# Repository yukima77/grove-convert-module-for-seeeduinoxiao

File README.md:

# Grove Convert Module for Seeeduino XIAO v1.0

Seeeduino XIAO用のGrove拡張基板です。

## 注意

本ページは基板に「Grove Convert Module for Seeeduino XIAO」という名称で書かれた基板用です。

シルク等の修正を行った「EdelBoard for Seeeduino XIAO」とかかれた基板は、下記ページを参照して下さい。
https://github.com/yukima77/edelboard-for-seeeduinoxiao

## 特長
入出力用・シリアル用・ws2812b/サーボモータ用の3つのコネクタが付いているシンプルな基板です。

Seeeduino XIAOを直付けすることによって、ピンヘッダーがあるときより薄くして使うこともできます。

ピン配置及び形状互換のAdafruit QT Pyも問題なく接続できます。

## スペック

基板サイズ（コネクタ込）：42.0×24.0×11.6 mm

## ピン

背面上部(ws2812b/サーボモータ用)：GND/VCC/D5(P5)/D4(P4)  
背面右部(シリアル用)：GND/3V3/TX(P6)/RX(P7)  
背面左部(入出力用)：GND/3V3/P1/P0

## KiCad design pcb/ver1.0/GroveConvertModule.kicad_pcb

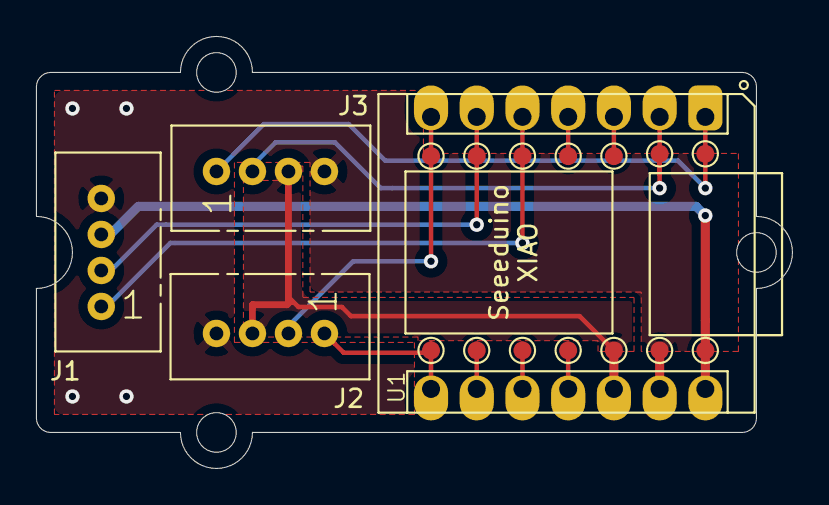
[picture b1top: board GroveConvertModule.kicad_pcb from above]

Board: 2 copper layers, 42.0 x 24.0 mm, 4 parts (0 on the bottom side), 9 nets.

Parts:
J1, J2, J3: Conn_01x04; Grove_1x04
U1: Seeeduino XIAO-MOUDLE14P-2.54-21X17.8MM_Header

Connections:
/3V3: J2.3, J3.3, U1.12
/5V: J1.3, U1.14
/A0_D0: J3.1, U1.1
/A1_D1: J3.2, U1.2
/A4_D4_SDA: J1.1, U1.5
/A5_D5_SCL: J1.2, U1.6
/A6_D6_TX: J2.2, U1.7
/A7_D7_RX: J2.1, U1.8
/GND: J1.4, J2.4, J3.4, U1.13

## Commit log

2021-04-02 Add the data of pcd.
2021-04-03 Add the file of docs.
2021-04-14 説明を追加
